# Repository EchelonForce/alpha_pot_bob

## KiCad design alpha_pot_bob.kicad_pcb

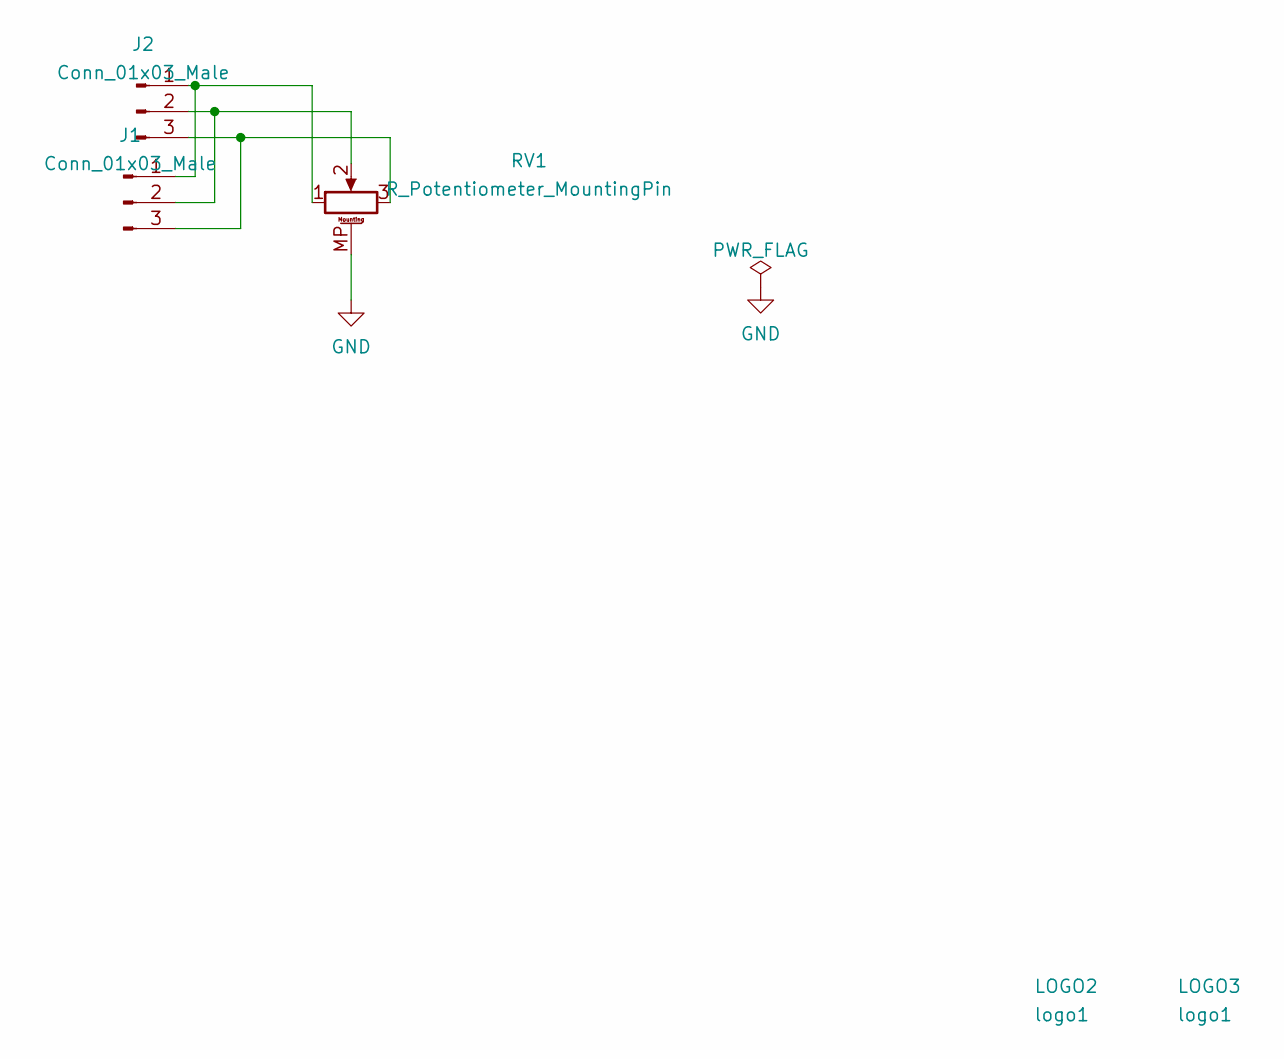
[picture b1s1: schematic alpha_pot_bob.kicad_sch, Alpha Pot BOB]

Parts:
J1, J2: Conn_01x03_Male; PinHeader_1x03_P2.54mm_Vertical
LOGO2: logo1; Logo1
LOGO3: logo1; Logo2
RV1: R_Potentiometer_MountingPin; Potentiometer_Alpha_RD901F-40-00D_Single_Vertical_w_3d

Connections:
GND: RV1.MP (MountPin)
unnamed: J1.1, J2.1, RV1.1
unnamed: J1.2, J2.2, RV1.2
unnamed: J1.3, J2.3, RV1.3

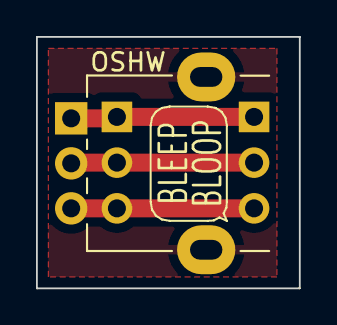
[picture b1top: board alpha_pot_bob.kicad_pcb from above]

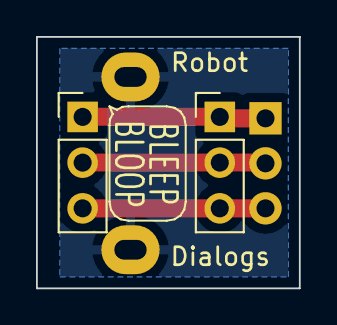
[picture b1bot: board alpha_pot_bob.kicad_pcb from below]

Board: 2 copper layers, 14.6 x 14.0 mm, 5 parts (2 on the bottom side), 3 nets.

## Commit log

2022-02-19 Initial commit with .gitignore
2022-02-19 Version 1 PCB as ordered
2022-08-31 Add readme
